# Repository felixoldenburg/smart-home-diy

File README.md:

# Smart Home DIY

Tracking the journey of creating custom build, µController based Smart Home components.  
Wiring them up to automatise repetitive scenarios for light and temperature.

- [Motivation](#motivation)
- [Next Steps](#next-steps)
  * [Error Handling](#error-handling)
- [Working Log](#working-log)
  * [Analysis and preparation of heater thermostat](#analysis-and-preparation-of-heater-thermostat)
  * [How to simulate rotary encoder signals with an Arduino?](#how-to-simulate-rotary-encoder-signals-with-an-arduino)
  * [Hook up the thermostat and set temperature](#hook-up-the-thermostat-and-set-temperature)
  * [Setup of a Adafruit HUZZAH ESP8266](#setup-of-a-adafruit-huzzah-esp8266)
  * [Scheduled wake up](#scheduled-wake-up)
  * [Setup OSX for Arduino and Feather Huzzah development in Arduino IDE](#setup-osx-for-arduino-and-feather-huzzah-development-in-arduino-ide)
- [Concept](#concept)
- [Characteristics](#characteristics)
- [Misc & Considerations](#misc---considerations)
- [Links](#links)
- [Paths](#paths)

## Motivation
Custom tailored smart home components with a focus on learning electronics and smart home concepts.
* Control lights and heating
* Safe money
* Automatise repetitve day to day tasks
* Avoid third party butt provider and limit/avoid internet exposure
* Reuse old/unused components

Just picking up an old box with electronic components got me started refreshing knowledge about transistors, µControllers, etc.

As many others I like to learn on the fly while working towards something new to learn or build. Instead of only digging into books and articles without the practical part.

It all started with ...  
"Hey, I got this cheap set of simple, but digital heater thermostats. I wonder if these could be modded to be controlled remotely."

## Glossary
Short Form | Meaning
---|---
HT | Heater Thermostat
BrainPi | RaspberryPi acting as gateway software
ES | ElasticSearch

## Next Steps

#### New / Unsorted
- Install new cable + plug for easier mounting and demounting between test runs
- Bug: The controller seems to crash regularly, as the restartCounter seems to be reset (starting from 0 again) all the time.  
  Try to enable all DEBUG logs. Check in monitor first or check how to persist the logs.
- Bug: Automatic thermostat (actual unit, not the controller) overrides temperature. HT doesn't recognise and keeps wrong temperature
- Analyse BrainPi logs from first test run
- Log system: ES on scaleway instance and BrainPi report to it

#### Reporting v1
1. BrainPi New endpoint: POST /heaterthermostat/<id>?temp=<value>&humidity=<value>
2. Refactor: BrainPi should report temperature instead of HT
3. Add basic auth to InfluxDB connection
4. Write outside temperature to InfluxDB from third party source (look for public API)
   1. Research public and free API to get temperature for city/region
   2. Python script as cronjob to write the outside temperature to InfluxDB 
5. Grafana Dashboard: Add humidity and outside temperature

##### Monitoring
###### Health checks
HT and BrainPi should both have health indicators showing if they work as expected and are up and running
###### Grafana Dashboard
Plot temperature, humidity and healthiness
###### Logging
Send logs from HT and BrainPi to an ElasticSearch instance (running on the BrainPi?)

### Error Handling
* A flashing FATAL lamp to indicate a severe error/exception like not having a Wifi connection
* Other errors are logged to ES
Indicate with red lamp if there was any error (later health check functionality)
* Remember errors and send to BrainPi which stores error messages in text file
  * Later send BrainPi logs from webserver and HT errors to ES on Scaleway instance

## Working Log
### Analysis and preparation of heater thermostat
1. Analyse heater thermostat -> It's using a rotary encoder, with 3 pins
2. Disassembling and re-assembling didn't damage the device! Phew..
3. Desolder rotary encoder and solder wires to the board AND DON'T damage these incredibly tiny SMD parts

### How to simulate rotary encoder signals with an Arduino
4. Read into topic of rotary encoder signals
5. Get inspirations, read about related material and instructions
6. Found code snippet that can simulate rotary encoder impulses via PWM

### Hook up the thermostat and set temperature
7. Wire up the thermostat and code, build, upload and test setting of temperature
8. Add buttons for manual single impulses, as the rotary encoder is also used for navigating the menu of the ts
9. Learn about pull-up and pull-down resistors necessary for proper button & LED wiring

The are microcontroller experimentation boards nowadays like the Arduino platform coming with all kinds of comforts.  
No need to take care of power supply and regulations, no need for wiring up a serial programmer, etc.  
Well, I really only know little and have few experience with electronic components, BUT
using the convenience of a platform like Arduino and quickly be able to proto type something really makes all the difference.  
Quicker achievements, more motivation!

### Setup of a Adafruit HUZZAH ESP8266 
As I wanted to keep my Arduino Uno for experimentation and needed some small device, ideally with some remote functionality, I decided to give the Adafruit HUZZAH ESP8266 a try.  
The Huzzah is well supported by the Arduino IDE and comes with a Wifi chip on board. Looking back chosing a Wifi based chip wasn't the best choice for a battery based setup. Wifi has a significantly higher energy consumption than 433Mhz, Bluetooth or LoRa based solutions.  
Still I'll continue to use it for now and will work with usb powered setup and try some deep sleep setup where the Huzzah wakes up every n minutes to send/receive data and control commands from a Raspberry Pi.  
See the link section on how to setup the Huzzah with the Arduino IDE.  
To start working with json based http calls the [ArduinoJson library](https://arduinojson.org/) is necessary which can be installed with the library manager of Arduino IDE

### Scheduled wake up
1. `ESP.deepSleep(microseconds);`
2. Connect the RST pin with GPIO16 via a 470Ohm or 1kOhm resistor

In order to safe energy on letting the Huzzah idle forever the chip knows different kinds of sleep modes.  
For the temperature control it's sufficient to only wake up every n minutes. In my case the controller should send the current temperature data to a time series db and read the target temperature it's supposed to set.  
Head over to https://randomnerdtutorials.com/esp8266-deep-sleep-with-arduino-ide/ for some nice tutorial and overview about the different sleep modes and how to use them.  
In my case I have a `ESP.deepSleep(10e6);` (the interval param is in µ seconds) at the end of the setup() method to set a sleep timer for 10s. 10s is for testing the code. Later a couple of minutes should suffice. This depends on how fine granular the desired tmp data should be recorded and how often the tmp should be adjusted.  
Normally for the controller to be restarted we'd need to pull the RST pin to ground (RST is always HIGH).
The timer will send a LOW signal to GPIO16. So if this pin is wired with the RST pin, the timer reset the controller after the interval and the controller will execute the setup() method again.  
Important: To be able to still flash the device "replace the wire by a 470R or 1K between GPIO16 and RES, which will allow the Serial-TTL to win."  
Otherwise the external reset from the Serial-TTL will fight against the HIGH of GPIO16.
This tip is from the user martinayotte@[www.esp8266.com](https://www.esp8266.com/viewtopic.php?p=60172#p60172)

### Setup OSX for Arduino and Feather Huzzah development in Arduino IDE
- To get the Arduino able to run on OSX the virtual COM port drivers are necessary for USB to serial communication.
See the link below to dowload. Install and reboot
- For the Huzzah to be accessible via USB Silabs usb-to-uart-bridge-vcp-drivers are necessary

## Concept
* Controlling lights and temperature in flat
* Low cost and low energy
* Track and optimise heating to save money
* Scenario - A Scenario defines a predefined set of actions or light setup

## Characteristics
- Don't talk to the internet! Specifically to any butt provider or company
- Aiming for simplicity

## Misc & Considerations
- Leverage iOS Homekit as UI

## Links
[Setup Arduino IDE for Adafruit Feather Huzzah ESP8266](https://learn.adafruit.com/adafruit-feather-huzzah-esp8266/using-arduino-ide)

[Getting started with the ESP8266 and DHT22 sensor](https://www.losant.com/blog/getting-started-with-the-esp8266-and-dht22-sensor)

[Install Virtual COM Port driver for Arduino IDE for OSX](https://www.ftdichip.com/Drivers/VCP.htm)

[usb-to-uart-bridge-vcp-drivers](https://www.silabs.com/products/development-tools/software/usb-to-uart-bridge-vcp-drivers)

## Paths
/Applications/Arduino.app/Contents/Java/hardware/tools/avr  
/Users/f.oldenburg/Library/Arduino15  
/Users/f.oldenburg/Documents/Arduino

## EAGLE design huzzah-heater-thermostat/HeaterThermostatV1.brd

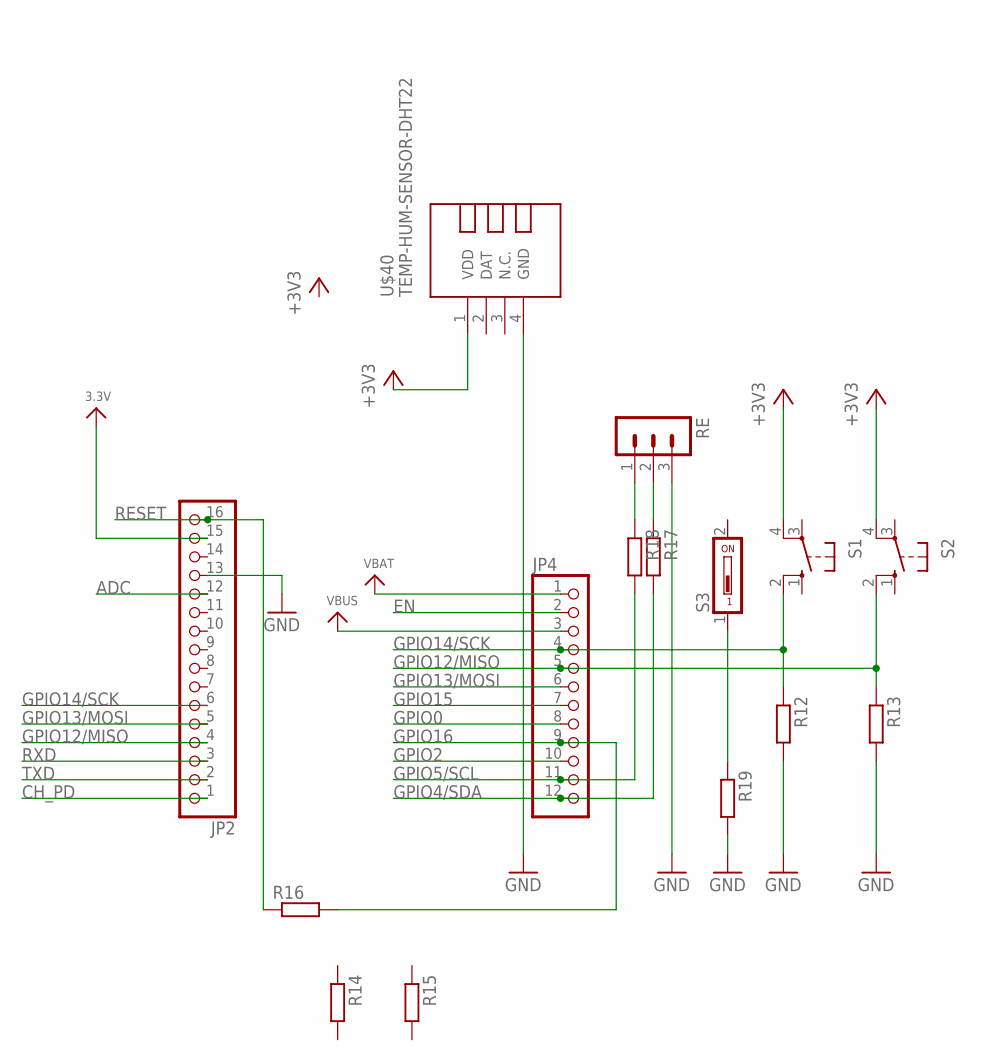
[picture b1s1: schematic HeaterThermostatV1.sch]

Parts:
JP2: HEADER-1X16ROUND; 1X16_ROUND
JP4: HEADER-1X12; 1X12_ROUND
R12, R13, R14, R15, R16, R17, R18, R19: R-EU_0207/10; 0207/10
RE: MA03-1
S1, S2: 10-XX; B3F-10XX
S3: DS01; DS-01
U$40: TEMP-HUM-SENSOR-DHT22

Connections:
3.3V: JP2.15
+3V3: S1.4 (P1), S2.4 (P1), U$40.1 (VDD)
ADC: JP2.12
CH_PD: JP2.1
EN: JP4.2
GND: JP2.13, R12.2, R13.2, R19.2, RE.3, U$40.4 (GND)
GPIO0: JP4.8
GPIO2: JP4.10
GPIO4/SDA: JP4.12, R17.2
GPIO5/SCL: JP4.11, R18.2
GPIO12/MISO: JP2.4, JP4.5, R13.1, S2.2 (S1)
GPIO13/MOSI: JP2.5, JP4.6
GPIO14/SCK: JP2.6, JP4.4, R12.1, S1.2 (S1)
GPIO15: JP4.7
GPIO16: JP4.9, R16.2
unnamed: R17.1, RE.2
unnamed: R18.1, RE.1
unnamed: R19.1, S3.1
RESET: JP2.16, R16.1
RXD: JP2.3
TXD: JP2.2
VBAT: JP4.1
VBUS: JP4.3

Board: 2 copper layers, 20 parts (4 on the bottom side), 12 nets, no tracks yet.

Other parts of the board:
U$7: ADAFRUIT_5MM
U$9: FEATHERLOGO
U$13: PCBFEAT-REV-040
U$15: ADAFRUIT_3.5MM
U$23: HUZZAHLOGO

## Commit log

2020-02-21 Update README.md
    Added initial project description
2020-02-22 Update README.md
    Added links section
2020-02-22 Update README.md
    Added paths
2020-02-29 Update README.md
    Added section about Huzzah setup with Arduino IDE
    Added scheduled wake up section
2020-03-01 Added raspberrypi-gateway with initial webserver script
2020-03-01 Added huzza-heater-thermostat with first draft of sketch
2020-03-01 Added statedment about installing OSX VCP driver
2020-03-01 Added instructions on setting up Arduino on OSX
2020-03-01 Added next steps
2020-03-01 Added table of contents
2020-03-02 wifi-controller can now simulate rotary encoder pulses (via buttons)
2020-03-02 wifi-controller: Added todo section
2020-03-02 wifi-controller Fixed button direction
2020-03-02 wifi-controller: Added basic error handling
2020-03-06 Put Wifi SSID + pwd into LocalConstants.h Ignore LocalConstants.h Reading temperature from remote
2020-03-07 Added go button to finish/skip init phase
2020-03-07 Updated README.md
    Fixed formatting
    Added sleep mode resistor tip
2020-03-07 First working setting of temp with +- 0.5
2020-03-07 Faster setting of temperature
2020-03-07 Now properly persisting the last known temperature in RTC memory
2020-03-07 Updated todos
2020-03-07 Replaced init button with a switch to be able to toggle the state back and forth
2020-03-07 Code clean up
2020-03-07 Added detailed next steps
2020-03-08 Fixing rotary encoder simulation Fixing accidentally changing temperature when gateway isn't reachable
2020-03-10 First draft EAGLE schematic for heater thermostat controller
2020-03-13 Reporting temperature sensor value and ping
2020-03-14 Finalised schematic
2020-03-15 Added new todos and two bugs

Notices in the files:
parts and their libraries:
microbuilder: This work is placed in the public domain, and may be freely used for commercial and non-commercial work with the following conditions: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
diy-modules: Released under the Creative Commons Attribution 4.0 International License: http://creativecommons.org/licenses/by/4.0
